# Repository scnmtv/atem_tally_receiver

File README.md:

# atem_tally_receiver
atem tally receiver - nrf24

IMPORTANT: library used - https://github.com/nRF24/RF24

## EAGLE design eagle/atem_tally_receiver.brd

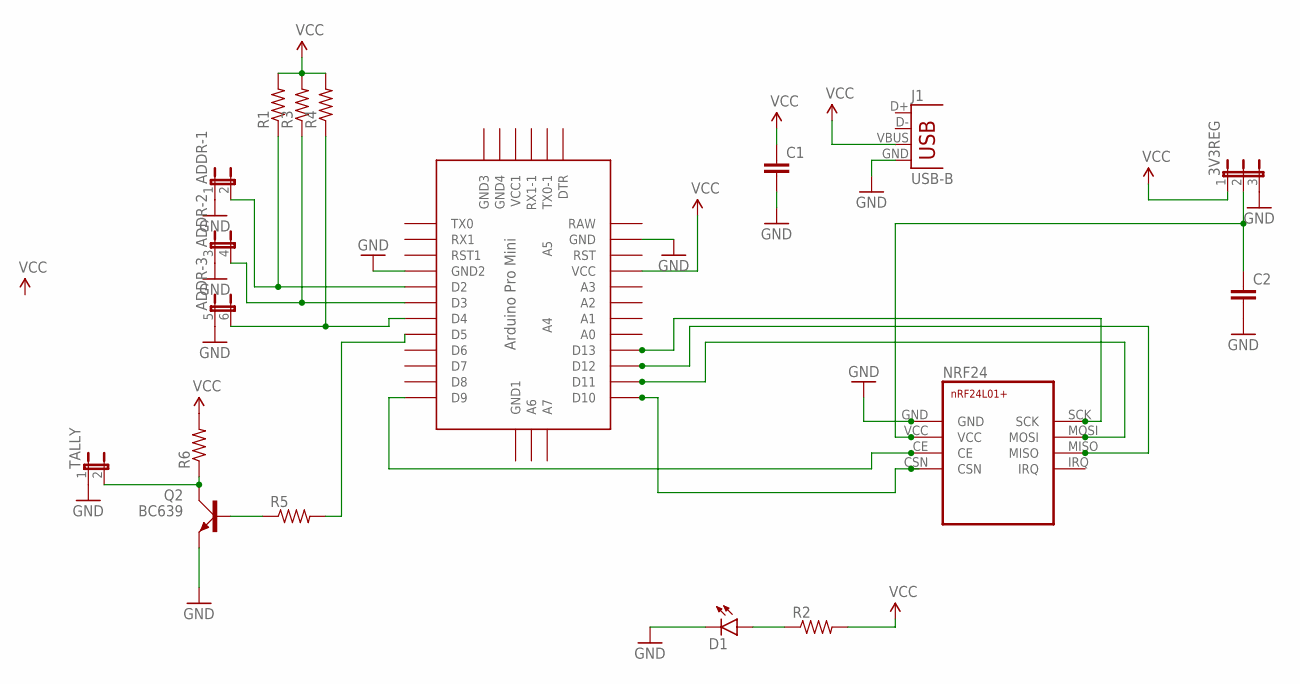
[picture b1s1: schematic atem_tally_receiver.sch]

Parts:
3V3REG: JP2E; JP2
ADDR: JP3QE; JP3Q
C1, C2: C-EU025-050X050; C025-050X050
D1: LED3MM
J1: USB-B; USB-B-PTH
NRF24: NRF24L01+
Q2: BC639; SOT54D
R1, R2, R3, R4, R5: RESISTORAXIAL-0.3; AXIAL-0.3
R6: RESISTORPTH-1W; AXIAL-0.6
TALLY: JP1E; JP1
U$1: ABK-PRO-MINI

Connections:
GND: 3V3REG.3, ADDR.1, ADDR.3 (1), ADDR.5 (1), C1.2, C2.2, D1.K (C), J1.GND, NRF24.GND, Q2.E, TALLY.1, U$1.GND, U$1.GND1 (GND2)
unnamed: NRF24.CE, U$1.D9
unnamed: NRF24.CSN, U$1.D10
unnamed: NRF24.SCK, U$1.D13
unnamed: NRF24.MOSI, U$1.D11
unnamed: NRF24.MISO, U$1.D12
unnamed: 3V3REG.2, C2.1, NRF24.VCC
unnamed: ADDR.2, R1.P$1 (1), U$1.D2
unnamed: ADDR.4 (2), R3.P$1 (1), U$1.D3
unnamed: ADDR.6 (2), R4.P$1 (1), U$1.D4
unnamed: D1.A, R2.P$1 (1)
unnamed: Q2.B, R5.P$1 (1)
unnamed: R5.P$2 (2), U$1.D5
unnamed: Q2.C, R6.P$1 (1), TALLY.2
VCC: 3V3REG.1, C1.1, J1.VBUS, R1.P$2 (2), R2.P$2 (2), R3.P$2 (2), R4.P$2 (2), R6.P$2 (2), U$1.VCC

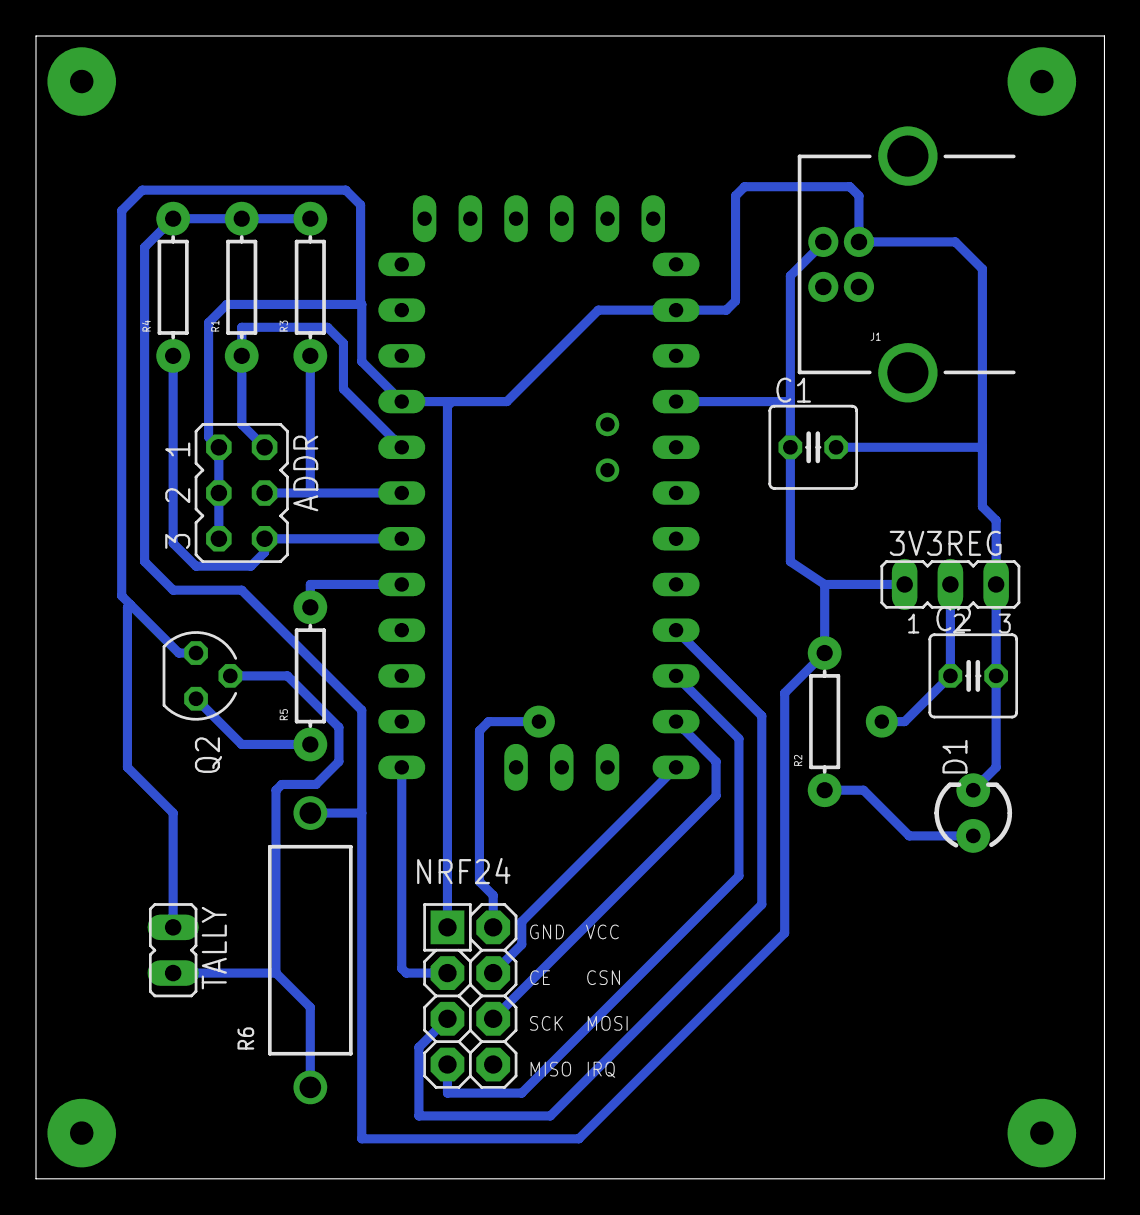
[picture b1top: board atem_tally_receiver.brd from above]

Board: 2 copper layers, 59.4 x 63.5 mm, 16 parts (0 on the bottom side), 15 nets.

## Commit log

2018-03-27 Create atem_tally_receiver.ino
    initial commit
2018-03-29 changed script, new HW
2018-03-29 Create TODO
2018-03-31 fixed receiving function and loop bug
2018-04-01 added channel selection option
2018-04-03 fixed pipes

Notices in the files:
parts and their libraries:
SparkFun-LED: Licensing: Creative Commons ShareAlike 4.0 International - https://creativecommons.org/licenses/by-sa/4.0
